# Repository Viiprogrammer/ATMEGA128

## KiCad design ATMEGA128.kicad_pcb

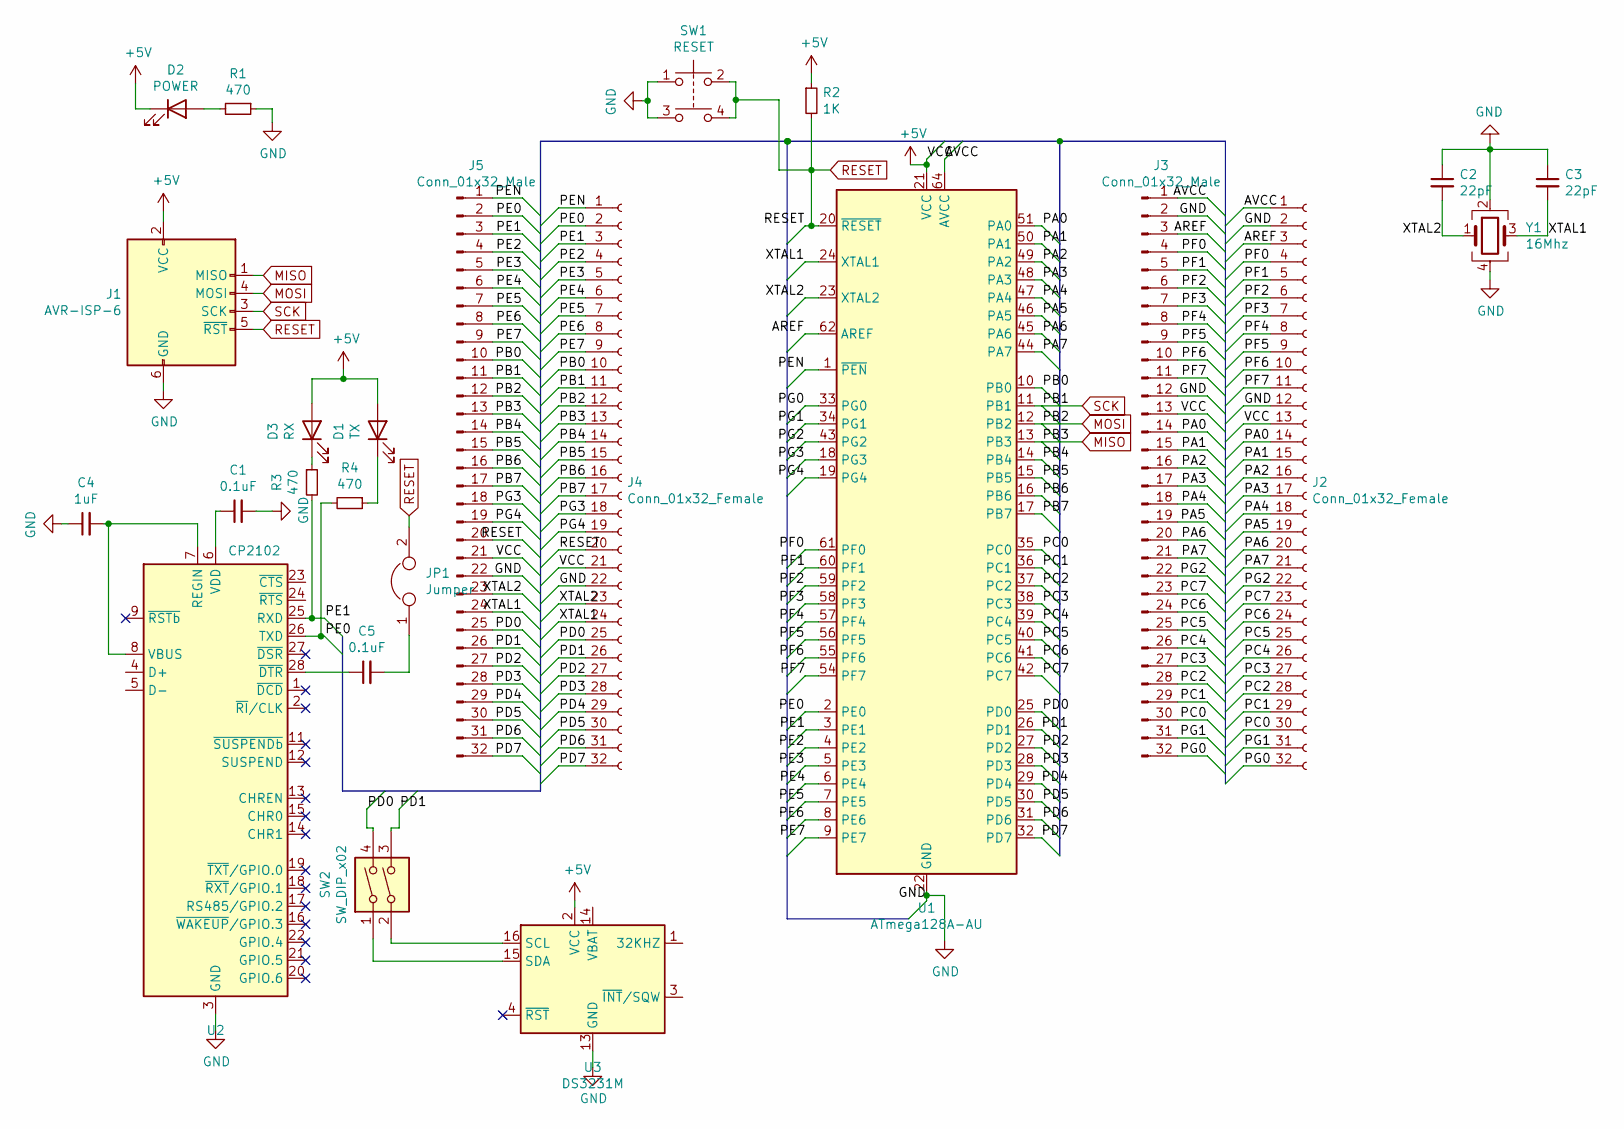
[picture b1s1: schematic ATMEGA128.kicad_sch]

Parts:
C1, C5: 0.1uF; C_0603_1608Metric
C2, C3: 22pF; C_0603_1608Metric
C4: 1uF; C_0603_1608Metric
D1: TX; LED_0805_2012Metric_Castellated
D2: POWER; LED_0805_2012Metric_Castellated
D3: RX; LED_0805_2012Metric_Castellated
J1: AVR-ISP-6; PinHeader_2x03_P2.54mm_Vertical
J2, J4: Conn_01x32_Female; PinHeader_1x32_P2.54mm_Vertical
J3, J5: Conn_01x32_Male; PinHeader_1x32_P2.54mm_Vertical
JP1: Jumper; PinHeader_1x02_P2.54mm_Vertical
R1, R3, R4: 470; R_0805_2012Metric
R2: 1K; R_0603_1608Metric
SW1: RESET; SW_SPST_TL3342
SW2: SW_DIP_x02
U1: ATmega128A-AU; TQFP-64_14x14mm_P0.8mm
U2: CP2102; QFN-28-1EP_5x5mm_P0.5mm_EP3.35x3.35mm
U3: DS3231M; SOIC-16W_7.5x10.3mm_P1.27mm
Y1: 16Mhz; Crystal_SMD_2016-4Pin_2.0x1.6mm

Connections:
/AREF: J2.3, J3.3, U1.62 (AREF)
/AVCC: J2.1, J3.1, U1.64 (AVCC)
/PA0: J2.14, J3.14, U1.51 (PA0)
/PA1: J2.15, J3.15, U1.50 (PA1)
/PA2: J2.16, J3.16, U1.49 (PA2)
/PA3: J2.17, J3.17, U1.48 (PA3)
/PA4: J2.18, J3.18, U1.47 (PA4)
/PA5: J2.19, J3.19, U1.46 (PA5)
/PA6: J2.20, J3.20, U1.45 (PA6)
/PA7: J2.21, J3.21, U1.44 (PA7)
/PB0: J4.10, J5.10, U1.10 (PB0)
/PB4: J4.14, J5.14, U1.14 (PB4)
/PB5: J4.15, J5.15, U1.15 (PB5)
/PB6: J4.16, J5.16, U1.16 (PB6)
/PB7: J4.17, J5.17, U1.17 (PB7)
/PD0: J4.25, J5.25, SW2.4, U1.25 (PD0)
/PD1: J4.26, J5.26, SW2.3, U1.26 (PD1)
/PD2: J4.27, J5.27, U1.27 (PD2)
/PD3: J4.28, J5.28, U1.28 (PD3)
/PD4: J4.29, J5.29, U1.29 (PD4)
/PD5: J4.30, J5.30, U1.30 (PD5)
/PD6: J4.31, J5.31, U1.31 (PD6)
/PD7: J4.32, J5.32, U1.32 (PD7)
/PE0: J4.2, J5.2, R4.2, U1.2 (PE0), U2.26 (TXD)
/PE1: J4.3, J5.3, R3.2, U1.3 (PE1), U2.25 (RXD)
/PE2: J4.4, J5.4, U1.4 (PE2)
/PE3: J4.5, J5.5, U1.5 (PE3)
/PE4: J4.6, J5.6, U1.6 (PE4)
/PE5: J4.7, J5.7, U1.7 (PE5)
/PE6: J4.8, J5.8, U1.8 (PE6)
/PE7: J4.9, J5.9, U1.9 (PE7)
/PEN: J4.1, J5.1, U1.1 (~PEN)
/PF0: J2.4, J3.4, U1.61 (PF0)
/PF1: J2.5, J3.5, U1.60 (PF1)
/PF2: J2.6, J3.6, U1.59 (PF2)
/PF3: J2.7, J3.7, U1.58 (PF3)
/PF4: J2.8, J3.8, U1.57 (PF4)
/PF5: J2.9, J3.9, U1.56 (PF5)
/PF6: J2.10, J3.10, U1.55 (PF6)
/PF7: J2.11, J3.11, U1.54 (PF7)
/PG0: J2.32, J3.32, U1.33 (PG0)
/PG1: J2.31, J3.31, U1.34 (PG1)
/PG2: J2.22, J3.22, U1.43 (PG2)
/PG3: J4.18, J5.18, U1.18 (PG3)
/PG4: J4.19, J5.19, U1.19 (PG4)
/PС0: J2.30, J3.30, U1.35 (PC0)
/PС1: J2.29, J3.29, U1.36 (PC1)
/PС2: J2.28, J3.28, U1.37 (PC2)
/PС3: J2.27, J3.27, U1.38 (PC3)
/PС4: J2.26, J3.26, U1.39 (PC4)
/PС5: J2.25, J3.25, U1.40 (PC5)
/PС6: J2.24, J3.24, U1.41 (PC6)
/PС7: J2.23, J3.23, U1.42 (PC7)
/XTAL1: C3.2, J4.24, J5.24, U1.24 (XTAL1), Y1.3
/XTAL2: C2.2, J4.23, J5.23, U1.23 (XTAL2), Y1.1
GND: C1.2, C2.1, C3.1, C4.1, J1.6 (GND), J2.2, J2.12, J3.2, J3.12, J4.22, J5.22, R1.1, SW1.1, SW1.3, U1.22 (GND), U1.53 (GND), U1.63 (GND), U2.3 (GND), U2.29 (GND), U3.5 (GND), U3.6 (GND), U3.7 (GND), U3.8 (GND), U3.9 (GND), U3.10 (GND), U3.11 (GND), U3.12 (GND), U3.13 (GND), Y1.2, Y1.4
MISO: J1.1 (MISO), J4.13, J5.13, U1.13 (PB3)
MOSI: J1.4 (MOSI), J4.12, J5.12, U1.12 (PB2)
unnamed: C1.1, U2.6 (VDD)
unnamed: C4.2, U2.7 (REGIN), U2.8 (VBUS)
unnamed: C5.1, U2.28 (~DTR)
unnamed: C5.2, JP1.1
unnamed: D1.1 (K), R4.1
unnamed: D2.2 (A), R1.2
unnamed: D3.1 (K), R3.1
unnamed: SW2.1, U3.15 (SDA)
unnamed: SW2.2, U3.16 (SCL)
RESET: J1.5 (~RST), J4.20, J5.20, JP1.2, R2.2, SW1.2, SW1.4, U1.20 (~RESET)
SCK: J1.3 (SCK), J4.11, J5.11, U1.11 (PB1)

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
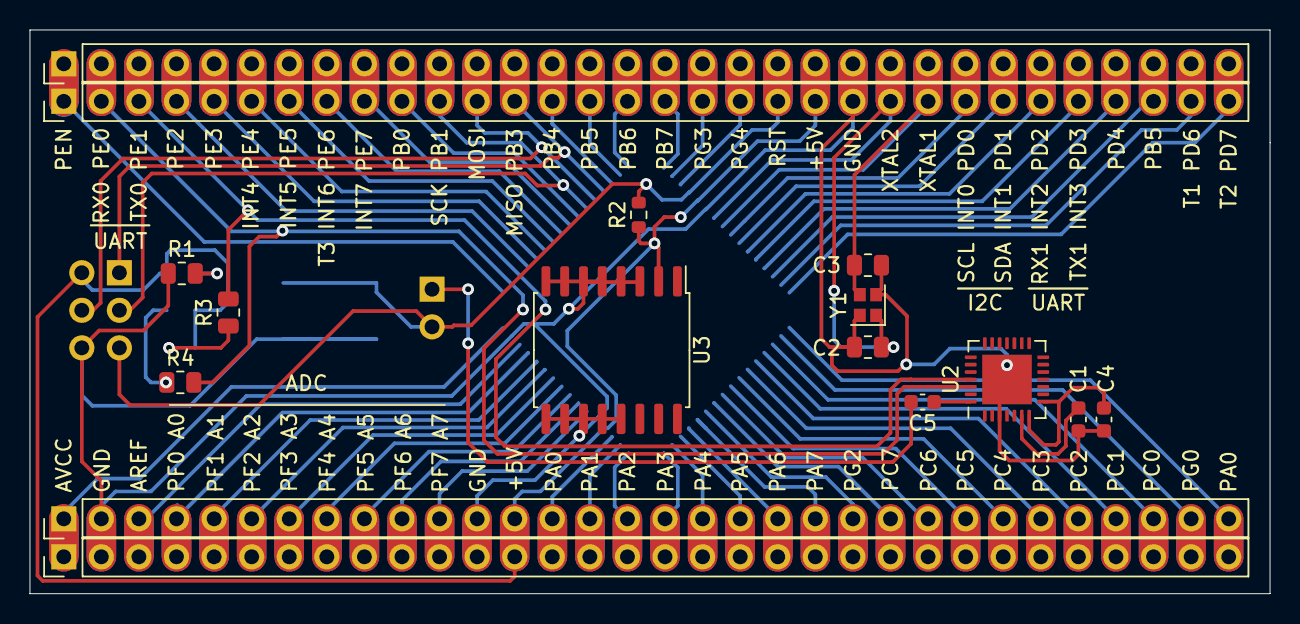
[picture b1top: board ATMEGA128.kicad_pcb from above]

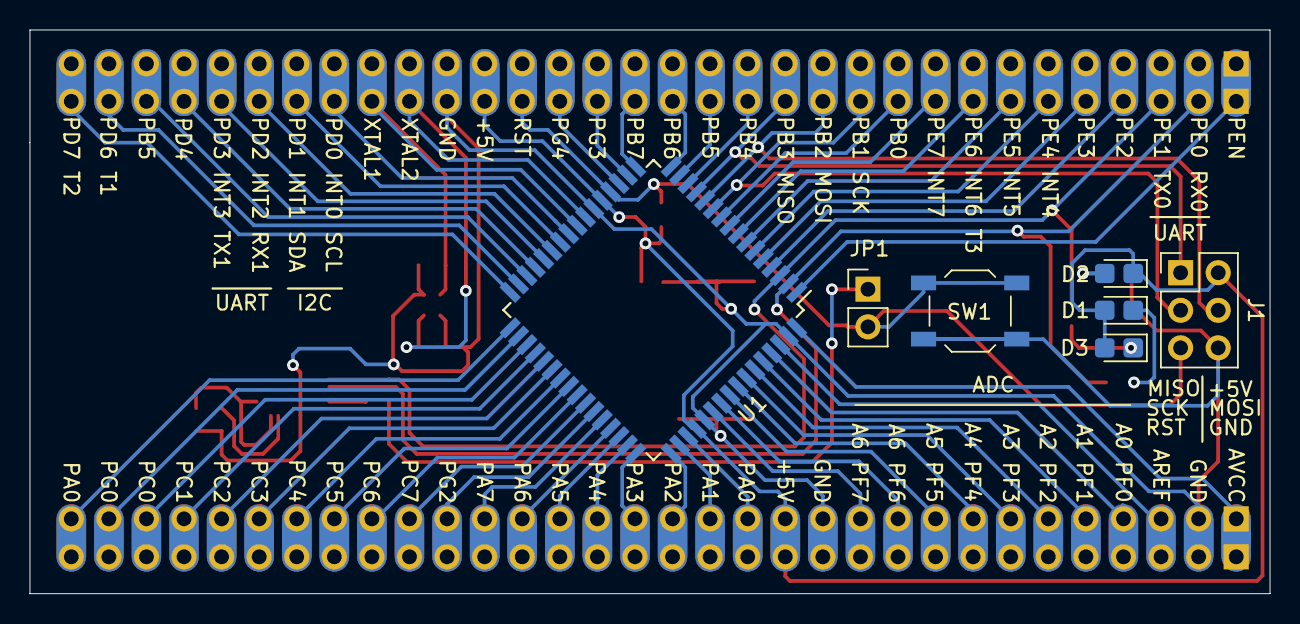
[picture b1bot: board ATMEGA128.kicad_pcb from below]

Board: 2 copper layers, 83.8 x 38.1 mm, 23 parts (7 on the bottom side), 68 nets.
